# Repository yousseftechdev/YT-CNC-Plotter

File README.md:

# YT CNC Plotter
This is a hobby project, it's basically a Mini CNC Plotter made using small 5v stepper motors and an Arduino Nano, I'll use it to draw circuits on copper plates to essentially make DIY single layer PCBs.

## Showcase

<br>

## How does it work?
It uses gear tracks the are moved by the stepper motors, two stepper motors are used to control the X and Y position of the pen and the third motor is used to control the Z position aka the up and down movement of the pen, a script will be used to translate normal G-Code that's used in big CNC machines into something the Arduino can understand.

## How to build?
All you need to do is print the PCB and solder the components specified in the Bill of Materials (BOM) section, or if you don't feel like printing the PCB just put all the components on a breadboard and follow the schematic in my [Journal](JOURNAL.md) for the wiring, then print the frame parts and mount the stepper motors to it and boom, you're done!

## BOM:

| Name                        | Price             | Quantity | Vendor       | Link                                                                                                                                                                                                                                                                                                                                                                                                                                                                                                                                                                                                        | Total Cost                                   |
| --------------------------- | ----------------- | -------- | ------------ | ----------------------------------------------------------------------------------------------------------------------------------------------------------------------------------------------------------------------------------------------------------------------------------------------------------------------------------------------------------------------------------------------------------------------------------------------------------------------------------------------------------------------------------------------------------------------------------------------------------- | -------------------------------------------- |
| Arduino Nano                | ~ 300 EGP         | 1        | Amazon Egypt | [Buy](https://www.amazon.eg/-/en/USB-Arduino-Nano-ATmega328P-Development/dp/B091CMTBF9/ref=sr_1_4?crid=1X8PQ2OLO66YQ&dib=eyJ2IjoiMSJ9.EfDcp_w5TllFTiPv8Fmw4C2VjlOaEKjOiOgfllqMe50VyvVQL165GiVDMQxeZAXarsJ2E95PXOaPtW48t9FeH5PbT_66gKC0o_ztq9BTszoHmayKxNGRTSRWmKhTIU3fsOuePUici85spu26k4xxLyfGFX4Fp57m7xmMx7Y4zb57hNCNhACnG9oMtYCq9yafMF50MA31HwlWvt4hQ-TkZAHA0010Lo856zYRkBGh8pjJP0Xe6N7Sp_cCJNtrQBcY7uGg6iuAfHmvlCNz8U0JhVqjkpi34Vc_PRv41a2vr4I.LRD6HcV5zoDo61TcB5b7rCggmHLi6al8yTJXp0ukraw&dib_tag=se&keywords=arduino+nano&qid=1749506924&sprefix=arduino+nan%2Caps%2C197&sr=8-4)                       | ~ 300 EGP                                    |
| 28BYJ-48 Stepper Motor      | 175 EGP           | 3        | Amazon Egypt | [Buy](https://www.amazon.eg/-/en/DIY-Kit-sourcingmap-28BYJ-48-5V-Phase-Stepper/dp/B0DZXWMGWK/ref=sr_1_13?crid=1ZMAWI7AFFZN&dib=eyJ2IjoiMSJ9.eOrVFMI6iFLPJhr676j4xB9pPxnW-4T21PyQg5wgpvAZACEMzFYdDeivv0Ch45w8zvDZn9DKJlhg5sDG_Br_Zh2GIYCIMzhs6-3RMghTAbzHnRgH_OeHmOcKgnlllamJaqZwsLMmypq_09LR4Zvk9lwa2npcaXmJGhA8iirrMDo8SxlYCvntoAtt-tj5Oqj-WWY6-hdqFvzdAN78V8sQ_EKXllu6kzGcCj7ADP2uLWyVqJG7-I_2h4T4HYTImIDun2VBtQ-nWEvvSSTvYOS84T9h6LiatnvO67Ss_DzSiSY.MvK00w2CuQ-y6f2SJ82isSjLGzd2rGOuaQliAOQx2ww&dib_tag=se&keywords=stepper+motor+28byj-48&qid=1749506700&sprefix=stepper+motor+28%2Caps%2C657&sr=8-13) | 525 EGP                                      |
| ULN2003A Motor Driver Chips | 64 EGP            | 2        | Amazon Egypt | [Buy](https://www.amazon.eg/-/en/ULN2003-Channel-Darlington-Sink-Driver/dp/B09H19L9BG/ref=sr_1_7?crid=2A00QN6JNISSG&dib=eyJ2IjoiMSJ9.lUAGuesIykr795jPOYUOLwVH2wUdnH6NCCIDKQK2L3duJI4GTb9pTRIGWzrgXqYs30Z7QftP5Tze_pWNRGjAiFhTN4zftXAU9xGvUW3XEWQjTo9T5N3K7v1yI7gWlYu13iBL3GgHgKR-yVLWsXuBA9engxNutE8G9g_E7_24bxLGgzuPMjdkX2OEqkerE_V3h2P1iHB-bA0j120EM5TbzmIb5INOcQ3TucjoeYI0gHQiWEBBv2s8cxgOWSqcjYlWLfSvv5MywFHED6bWaeVef4RLu5KYxxBy95l2oKNa17Y.rE7ydz17I_rLUPg89nhEBNpok9knCQd32RCZrPQjdZ8&dib_tag=se&keywords=uln2003&qid=1749507201&sprefix=uln200%2Caps%2C257&sr=8-7)                                  | 128 EGP                                      |
| 100 nF Capacitors           | 45 EGP            | 2        | Amazon Egypt | [Buy](https://www.amazon.eg/-/en/10Pcs-Ceramic-Capacitor-0-1uf-100nf/dp/B09HZGRMS6/ref=sr_1_2?crid=2NIOVEKPVDUGQ&dib=eyJ2IjoiMSJ9.XAfo3SoL0K2Zsg_268kmgSMA-tRhkBtr-xyZMfh8CYEzQcCvqKSKxu9gQsu155kBfmsBMdhFhxvCDWU7c0N4IaJJq2GQ-GLlgoBLwyAHfvXXf7FdOwdWt2JOBu9YbGkXhyPbN6-Wy58rdsspTU0DYpOjw2fLLpI2fdjC9j2d-M9dr0YkWFoamw6z7o26c3CKNJv-5VGYvrnnUBP0TtDXOG-zJx3j-2MK95FYX-XXDKih3jk1qmCHxJPeQaH8pK-zYb2S6-oREgQGGhrcN6qcsookaJNaJg7WMF2iaTyJKcA.AqJwUernq0nFuDJzyW3KL5Zpwj7GrVrAYE0ZBAfTso4&dib_tag=se&keywords=100nf+capacitor&qid=1749507416&sprefix=100nF%2Caps%2C217&sr=8-2)                              | 90 EGP                                       |
| 100 uF Capacitor            | 26.5 EGP          | 1        | Amazon Egypt | [Buy](https://www.amazon.eg/-/en/Other-100uF-25V-Round-Capacitor/dp/B091D7ZC4C/ref=sr_1_1?crid=2BH7P37IZQ7RW&dib=eyJ2IjoiMSJ9.aGcHw6zBqdnAdgR3tnjA0eSN5cu2m3lcLWuA_TI0A1y1kLtRLkrBKvzSkDBdKU-ZGJ_fUH3dUzXSGzCpNCAH8fiKBDWkIZXMN6Qq72lbRiLZ6ZIN03hD5DpKdVO9w7g1ifOJ-rI6AKR4Zj3H0CEt9R4OY55VwUKOgxMLwADlg00MLnvQH4wftYjbAG95fKXU.SVahB9nwrM5pOqaerPRTGPUB_0fd3GTT330bWDMyTuo&dib_tag=se&keywords=100uf+capacitor&qid=1749507607&refinements=p_36%3A-2900&rnid=22080723031&sprefix=100uF+capac%2Caps%2C598&sr=8-1)                                                                                             | 26.5 EGP                                     |
| JST HX 5 Pin connector      | 44 EGP            | 3        | Amazon Egypt | [Buy](https://www.amazon.eg/-/en/DIY-kit-Data-Terminal-Connector-2-54mm/dp/B0F2GB82ZZ/ref=sr_1_19?crid=28Y7O1ONDEG6U&dib=eyJ2IjoiMSJ9.4g0TJDbISJ6t5kpIOh1IYZXkjJeIM8T1t7qWSz-ad9wloHwVy-lBdXtdwVLtHQL1Xf9jwLjJ-wrPJWPC51nJkX2sx94JFBcKQRRdvjtIc00-pCzWgbn8wc1xx2KSWH74FFaNYgemVUX4SOBjCw6DCjxHcsF45HIyGRGakPjBxlr6Oe8lfPImLD3ruNg9_gEp_XYZZv3kpbF4n6nYpoErNi5awjFNCSYa_ksKgRPWinZipJ4ORuXksNnTGgSmluPce9b0LpsjdBRHD5qKhUu5DhuueFHqvBwYZk0emXKRBfg.Rxg10TP8r92GwoRjT0pebtwGluqG2TfnPOu5wtTo1PI&dib_tag=se&keywords=JST+XH&qid=1749509392&sprefix=jst+xh%2Caps%2C417&sr=8-19)                                 | 132 EGP                                      |
| 5v Adapter                  | 52.25 EGP         | 1        | Amazon Egypt | [Buy](https://www.amazon.eg/-/en/AC-DC-Adapter-5V-1A/dp/B091D28XJ7/ref=sr_1_1?crid=E1ORCM362D7W&dib=eyJ2IjoiMSJ9.OKgOa-2qfRaqdKfrbOwmpayX5TRIKwCDcbp1FRjG2hrensPHfPDK3yryc0MmzUDTNz4bGxr68LL_PJ9LqA5nJxI5PUP3C_kfRVBcGKCtiuvw3ecpKQxzAxB8iSAMOFzPY-opqkkyuOQ-41B1g8x-YRnPjfE4Qnh7lIoMR7rHgWfs3x9zY_HleO6s0TCPN5ADyxn-5u5Unr4gG4uCckmLu3GBnbC69H_8UPIw4L64vNMZ2XqYyEuYv1tY4wx1wnvo9y3CQFGjEaRvwtaNmQjrJUQ0gZUV3g0Tm7z3FHY8kpQ.TL7s69lnZUjsKReXCvVZZYnDVvNDbPX0rOxqUxIeSYM&dib_tag=se&keywords=5v+adapter&qid=1749512550&sprefix=5v+adapter%2Caps%2C156&sr=8-1)                                               | 52.25 EGP                                    |
| Barrel Jack                 | 130 EGP           | 1        | Amazon Egypt | [Buy](https://www.amazon.eg/-/en/5PCS-Charging-Connector-Universal-Replacement/dp/B09RVZVZ9V/ref=sr_1_34?crid=1NRQT80DPQQ3L&dib=eyJ2IjoiMSJ9.8psoMaVTIHlm98Zth3jmYCPxO0O9ipjs8cuK3OvU3lxA08e0f10jv90MYrDRvSeWeBX-9vU46QBehWvNivcpFSSPnr2XTGg45wRT6U-Oag2XaSZ7zLEbwbZQPZ3xl-1qngYnsDwi4V6e9lQy1uZvYOk6UU6pGeVESF1T8Jad06dHPn3PnU2-Uj_RJU-d8ZhaBNBuHHglhPawOSlZrSHkwJIwUbIXSSIxjSEpeYaz6o3MZzPPG-4p8qAkN6R652Y-_DvYlEnVX290n8CgHUh4x_h1RZCKCiOCL6BkVB_QfyM.tZynJrXtU5oRl7FOn_rnpQrfjvceUzTLS8LyS8-S8f4&dib_tag=se&keywords=barrel+connector&qid=1749512335&sprefix=barrel+%2Caps%2C187&sr=8-34)               | 130 EGP                                      |
| Female Pin headers          | 52 EGP            | 1        | Amazon Egypt | [Buy](https://www.amazon.eg/-/en/Female-Pin-Header-1x40Pin-2-54mm/dp/B0CJYGZXSY/ref=sr_1_1?crid=28SURV8ACVVCZ&dib=eyJ2IjoiMSJ9.rQbHkLgoMjqFuT9zHnBBOdIMTkf9pwrmS6_8F-ZIYb3solj3uTqFAmrdapoouOsxZYyoXPGwn50OLcqGBB5GMxRPgLztBlAzOEBXzJnCw0-CIUSv5CC2HCuQAIzHHBRdr_L57HyrueeSbL9cSv4d5iCC0UtzjSSB3Yz0yIR4Bryb0-H439tPXgA4BNDX0Vhzsy4ZZm62hygO6aYwfUn0usDc7mxMKm6Min2PnCrLwQMGfKao0aw25-naqGgleQupBiLRruBnH868pbRJW8rhqsaMePTvVA3bQu5wYEkgSmw.NAueoGOSDd6pZ9hQm_M82SftCnan7Z9lXhVqhuNohIY&dib_tag=se&keywords=female+pin+headers+1x15&qid=1749514539&sprefix=female+pin+headers+1x15%2Caps%2C139&sr=8-1)       | 52 EGP                                       |
| 3D Printing                 | Depends on vendor |          |              |                                                                                                                                                                                                                                                                                                                                                                                                                                                                                                                                                                                                             | Depends on vendor                            |
| PCB Manufacturing           | Depends on vendor |          |              |                                                                                                                                                                                                                                                                                                                                                                                                                                                                                                                                                                                                             | Depends on vendor                            |
|                             |                   |          |              |                                                                                                                                                                                                                                                                                                                                                                                                                                                                                                                                                                                                             | Grand total:<br><br>1303.75 EGP or 26.33 USD |

## What have I learned?

I have learned so much about CAD from making this project, this has been such a great learning experience, but the most important thing I've learned is not to use Fusion 360 ever again.

Note: If you want to print the STL files please scale them down, Fusion messed up when exporting.

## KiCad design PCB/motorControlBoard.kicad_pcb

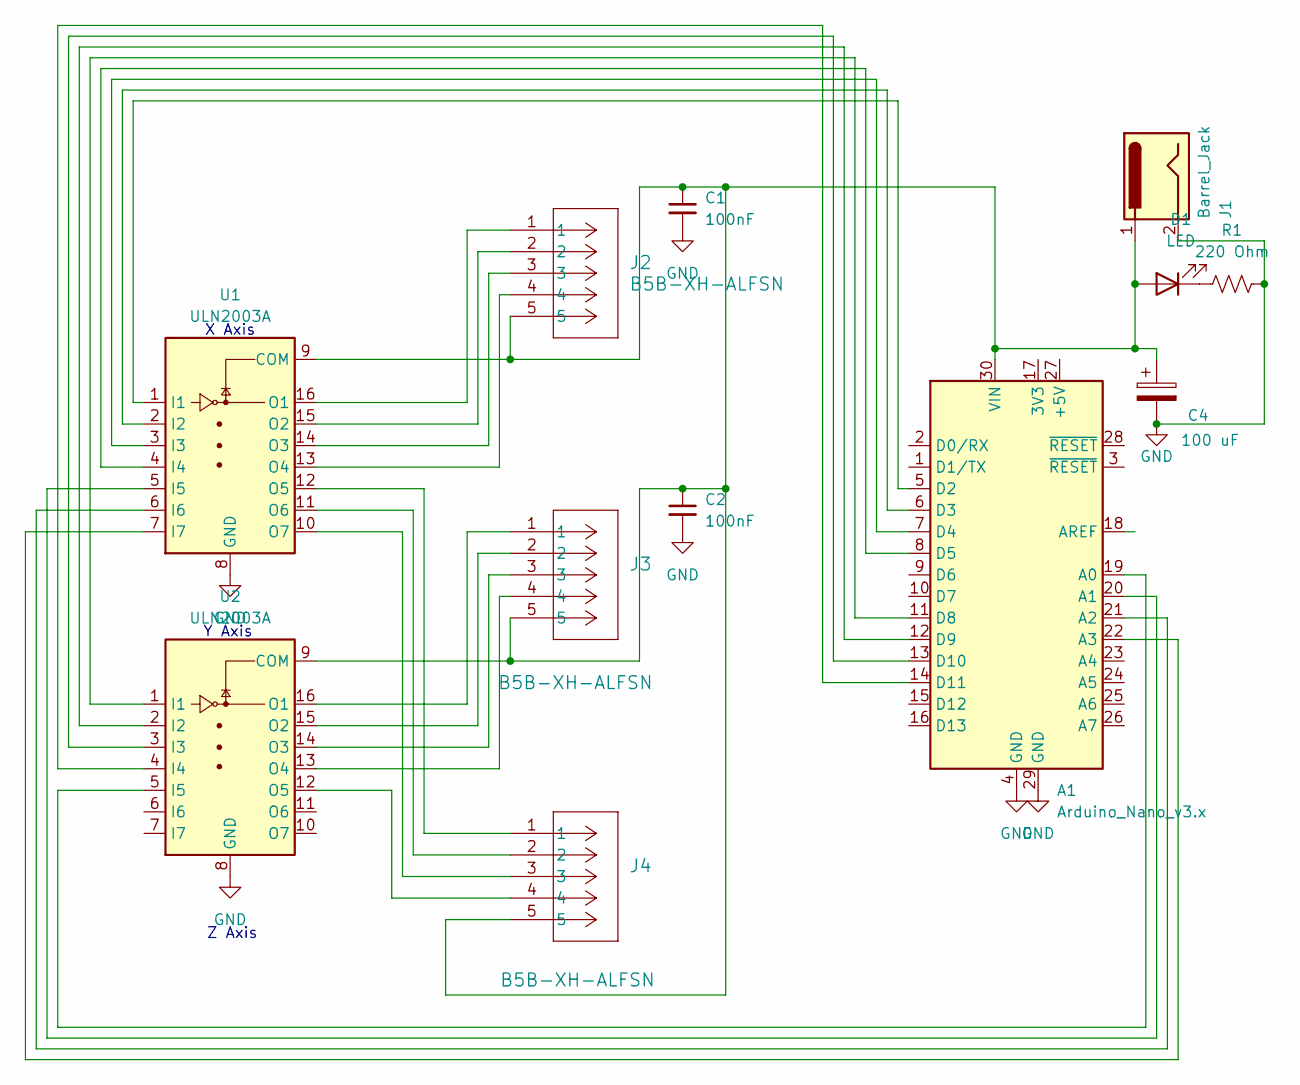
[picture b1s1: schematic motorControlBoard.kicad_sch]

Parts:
A1: Arduino_Nano_v3.x; Arduino_Nano
C1, C2: 100nF; C_Disc_D5.0mm_W2.5mm_P5.00mm
C4: 100 uF; CP_Radial_D6.3mm_P2.50mm
D1: LED; LED_D5.0mm
J1: Barrel_Jack; BarrelJack_Horizontal
J2, J3, J4: B5B-XH-ALFSN; JST_XH_B5B-XH-A_1x05_P2.50mm_Vertical
R1: 220 Ohm; R_Axial_DIN0204_L3.6mm_D1.6mm_P7.62mm_Horizontal
U1, U2: ULN2003A; DIP-16_W7.62mm

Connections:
GND: A1.4 (GND), A1.29 (GND), C1.2, C2.2, C4.2, J1.2, R1.2, U1.8 (GND), U2.8 (GND)
unnamed: A1.19 (A0), U2.5 (I5)
unnamed: A1.20 (A1), U1.5 (I5)
unnamed: A1.21 (A2), U1.6 (I6)
unnamed: A1.22 (A3), U1.7 (I7)
unnamed: A1.5 (D2), U1.1 (I1)
unnamed: A1.6 (D3), U1.2 (I2)
unnamed: A1.7 (D4), U1.3 (I3)
unnamed: A1.8 (D5), U1.4 (I4)
unnamed: A1.11 (D8), U2.1 (I1)
unnamed: A1.12 (D9), U2.2 (I2)
unnamed: A1.13 (D10), U2.3 (I3)
unnamed: A1.14 (D11), U2.4 (I4)
unnamed: A1.30 (VIN), C1.1, C2.1, C4.1, D1.2 (A), J1.1, J2.5, J3.5, J4.5, U1.9 (COM), U2.9 (COM)
unnamed: D1.1 (K), R1.1
unnamed: J2.1, U1.16 (O1)
unnamed: J2.2, U1.15 (O2)
unnamed: J2.3, U1.14 (O3)
unnamed: J2.4, U1.13 (O4)
unnamed: J4.1, U1.12 (O5)
unnamed: J4.2, U1.11 (O6)
unnamed: J4.3, U1.10 (O7)
unnamed: J3.1, U2.16 (O1)
unnamed: J3.2, U2.15 (O2)
unnamed: J3.3, U2.14 (O3)
unnamed: J3.4, U2.13 (O4)
unnamed: J4.4, U2.12 (O5)

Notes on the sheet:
Y Axis
X Axis
Z Axis

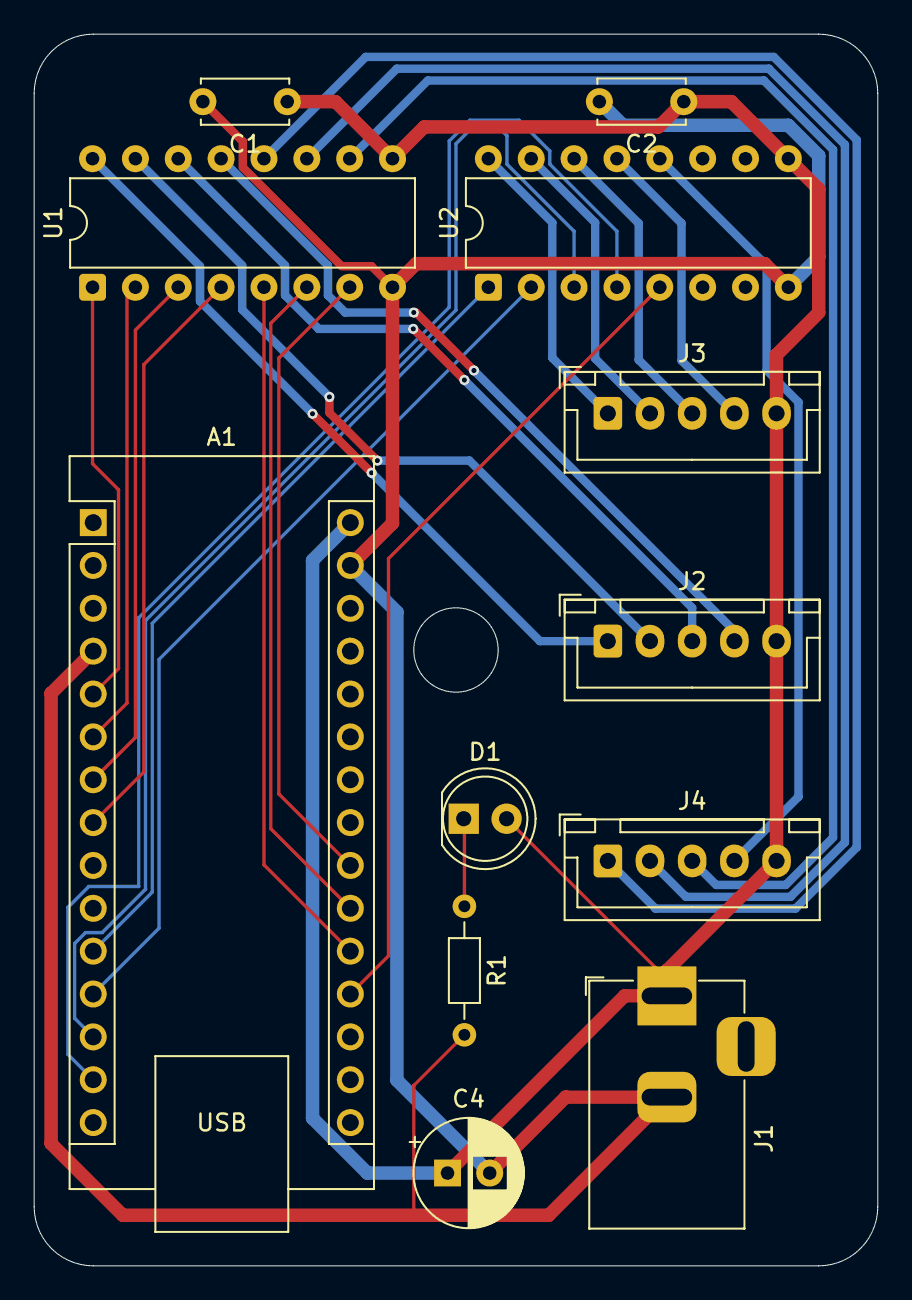
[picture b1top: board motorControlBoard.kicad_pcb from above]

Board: 2 copper layers, 50.0 x 73.0 mm, 12 parts (0 on the bottom side), 27 nets.

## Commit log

2025-06-09 Made parts list and designed controller PCB
2025-06-10 correction to last commit
2025-06-10 removed temp file
2025-06-10 Refined PCB and finished frame
2025-06-11 final (i think)
2025-06-11 final final
2025-06-11 final final final
2025-06-11 Added note at the bottom, please read.
2025-06-11 Added same note to README
2025-06-11 added images of final product
2025-06-11 minor details
2025-06-11 Adding submission requirements
2025-06-12 port holes in the case
